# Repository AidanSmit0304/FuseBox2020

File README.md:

# FuseBox2020
Wazzu Racing Fusebox for 2020 Racecar

EAGLE:
.brd file for PCB, 
 .sch file for schematic, 
  zip file for PCB Manufacturing

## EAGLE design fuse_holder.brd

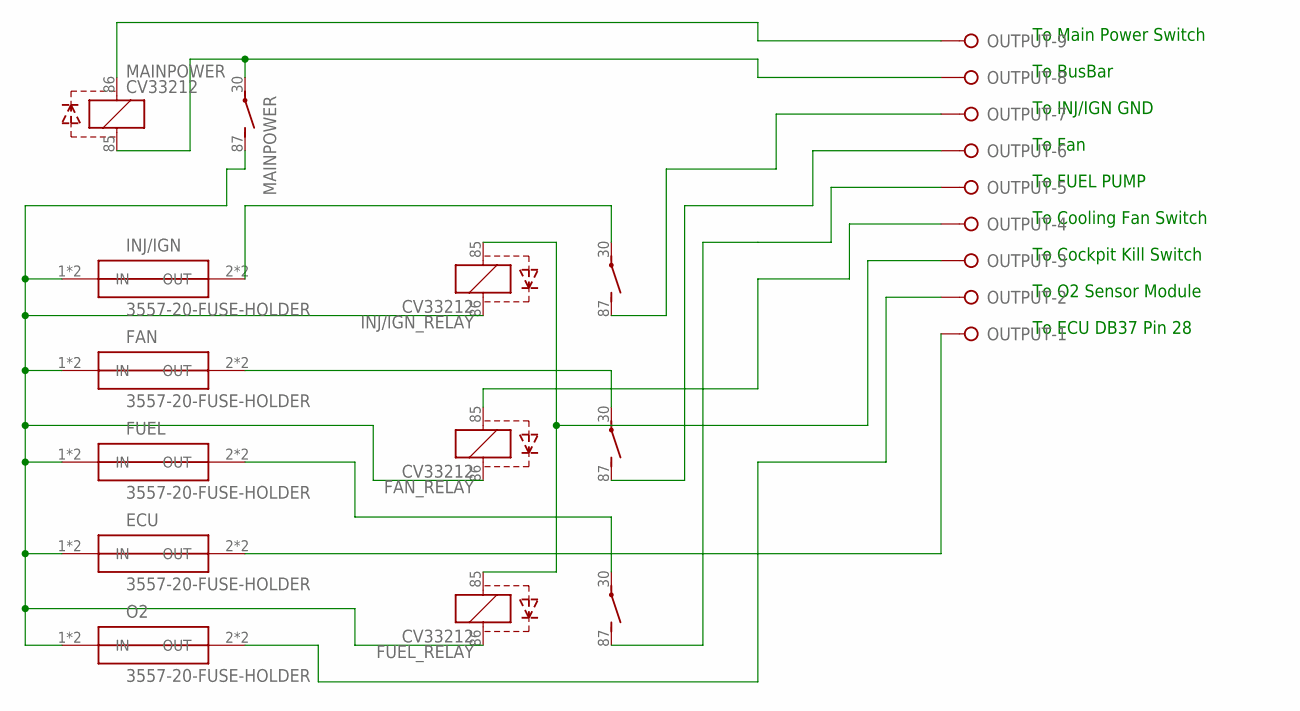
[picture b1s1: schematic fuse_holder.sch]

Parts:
ECU: 3557-20-FUSE-HOLDER
FAN: 3557-20-FUSE-HOLDER
FAN_RELAY: CV33212; CV1A-MICRO-280
FUEL: 3557-20-FUSE-HOLDER
FUEL_RELAY: CV33212; CV1A-MICRO-280
INJ/IGN: 3557-20-FUSE-HOLDER
INJ/IGN_RELAY: CV33212; CV1A-MICRO-280
MAINPOWER: CV33212; CV1A-MICRO-280
O2: 3557-20-FUSE-HOLDER
OUTPUT: W237-09P; W237-9P

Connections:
INJ/IGN_RELAY: ECU.1 (IN), ECU.3 (IN), FAN.1 (IN), FAN.3 (IN), FAN_RELAY.86 (+), FUEL.1 (IN), FUEL.3 (IN), FUEL_RELAY.86 (+), INJ/IGN.1 (IN), INJ/IGN.3 (IN), INJ/IGN_RELAY.86 (+), MAINPOWER.87 (S), O2.1 (IN), O2.3 (IN)
unnamed: MAINPOWER.86 (+), OUTPUT.9
unnamed: MAINPOWER.30, MAINPOWER.85 (-), OUTPUT.8
unnamed: INJ/IGN.2 (OUT), INJ/IGN.4 (OUT), INJ/IGN_RELAY.30
unnamed: FAN.2 (OUT), FAN.4 (OUT), FAN_RELAY.30
unnamed: FUEL.2 (OUT), FUEL.4 (OUT), FUEL_RELAY.30
unnamed: INJ/IGN_RELAY.87 (S), OUTPUT.7
unnamed: FAN_RELAY.87 (S), OUTPUT.6
unnamed: FUEL_RELAY.85 (-), INJ/IGN_RELAY.85 (-), OUTPUT.3
unnamed: FAN_RELAY.85 (-), OUTPUT.4
unnamed: O2.2 (OUT), O2.4 (OUT), OUTPUT.2
unnamed: ECU.2 (OUT), ECU.4 (OUT), OUTPUT.1

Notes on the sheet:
To BusBar
To Main Power Switch
To INJ/IGN GND
To Fan
To FUEL PUMP
To Cooling Fan Switch
To Cockpit Kill Switch
To O2 Sensor Module
To ECU DB37 Pin 28

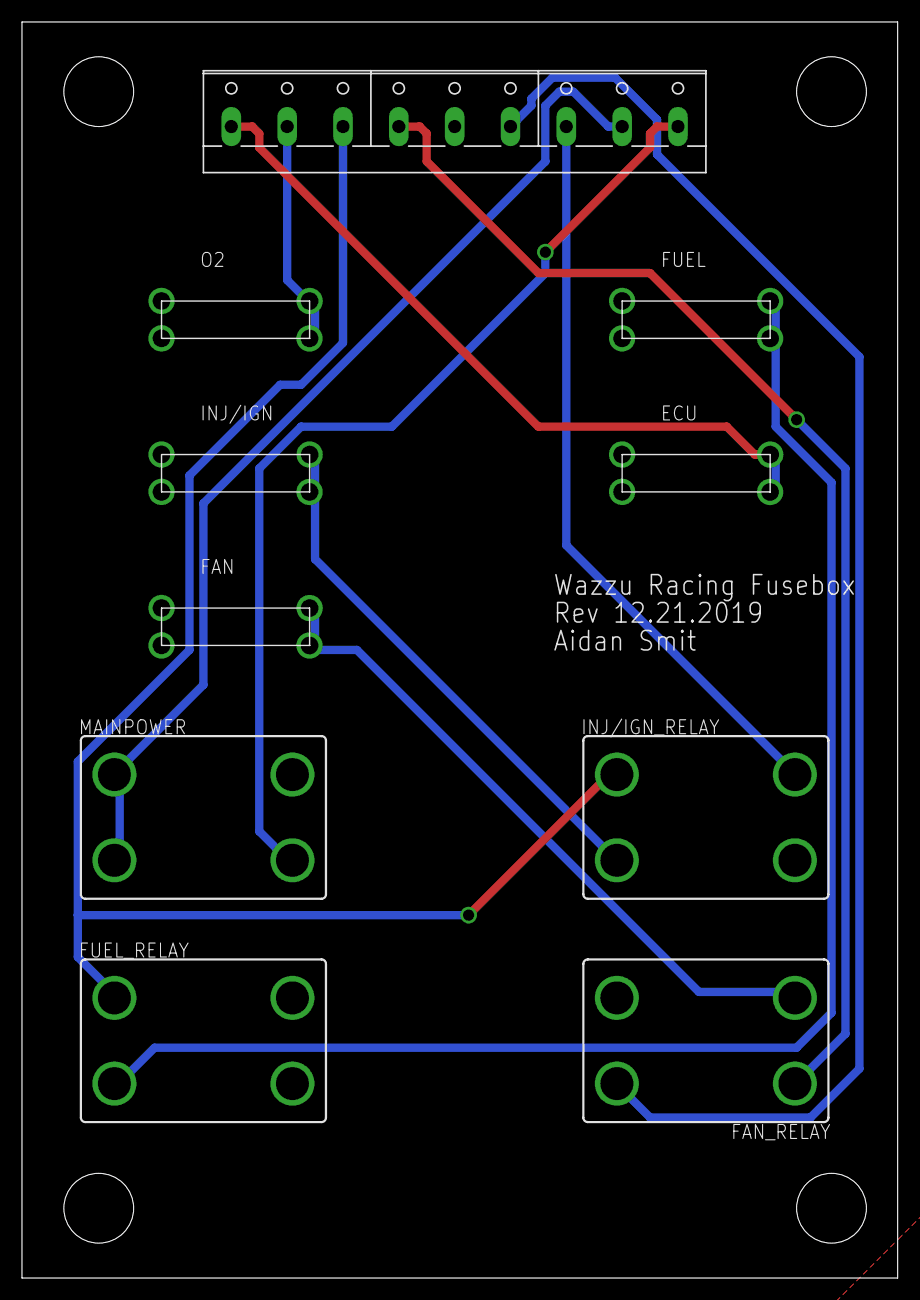
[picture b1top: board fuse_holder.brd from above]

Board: 2 copper layers, 79.7 x 114.3 mm, 10 parts (0 on the bottom side), 12 nets.

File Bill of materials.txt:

Partlist

Exported from fuse_holder.brd at 12/21/2019 8:13 PM

EAGLE Version 9.1.3 Copyright (c) 1988-2018 Autodesk, Inc.

Assembly variant: 

Part          Value               Package             Library      Position (inch)       Orientation

ECU           3557-20-FUSE-HOLDER 3557-20-FUSE-HOLDER FSAE         (2.5 2.7)             R0
FAN           3557-20-FUSE-HOLDER 3557-20-FUSE-HOLDER FSAE         (0.85 2.15)           R0
FAN_RELAY     CV33212             CV1A-MICRO-280      relay        (2.8 0.6)             R180
FUEL          3557-20-FUSE-HOLDER 3557-20-FUSE-HOLDER FSAE         (2.5 3.25)            R0
FUEL_RELAY    CV33212             CV1A-MICRO-280      relay        (1 0.6)               R0
INJ/IGN       3557-20-FUSE-HOLDER 3557-20-FUSE-HOLDER FSAE         (0.85 2.7)            R0
INJ/IGN_RELAY CV33212             CV1A-MICRO-280      relay        (2.8 1.4)             R0
MAINPOWER     CV33212             CV1A-MICRO-280      relay        (1 1.4)               R0
O2            3557-20-FUSE-HOLDER 3557-20-FUSE-HOLDER FSAE         (0.85 3.25)           R0
OUTPUT                            W237-9P             con-wago-508 (1.9 3.9)             R0
